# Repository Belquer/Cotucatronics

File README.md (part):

# Cotucatronics OS
<!-- doc-check: ignore no_connect (KiCad ERC violation code) -->
<!-- doc-check: ignore dentro_do_contorno (tool lives in kicad/, out of check_docs' reach) -->
<!-- doc-check: ignore para_fabrica (tool lives in kicad/, out of check_docs' reach) -->
<!-- doc-check: ignore pcb_contorno (tool lives in kicad/, out of check_docs' reach) -->

<!-- doc-check: ignore hook_stop (script in docs/operacao/, not a param) -->
<!-- doc-check: ignore svg_colisoes (tool outside src/. check_docs sweeps `src/`; these live in `tools/`, `docs/desenhos/caixa/` or `kicad/cotuca_cerebro/`, which it does not read. Not a phantom: it is the checker's reach.) -->

Modular firmware for **sound-sculpture instruments**. The core idea is that the
same brain runs any sculpture: the instrument code is board-agnostic, and
changing hardware means writing one new file — not rewriting the system.

A collaborative project.

> ### Status, 2026-09-04 — **v0.301.0**
>
> **480 MHz · 48 kHz · block 48** (1,000 µs deadline) · app in QSPI
>
> **Two character chains** (drive, phaser, warble, tarolator per piezo) over a
> **shared tail** (delay, freeze, shimmer↺reverb), with a **2×2 routing
> matrix** — which chain feeds which output.
>
> **Four-layer anti-feedback stack**, all in shell C++: gate, Governor, limiter
> and SSB shifter — plus **SuMiA™**, the automated microphonic-feedback
> suppressor, four notches per branch, which hunts and fills on its own.
>
> **MIDI across six channels** over a BLE↔UART bridge on an ESP32-C3 (`ch1`
> shared · `ch2` chain A · `ch3` chain B · listen = send + 3), **81 CCs**,
> presets in RAM, **black box** in BACKUP_SRAM.
>
> **Panel soldered and alive:** SSD1309 OLED over SPI with an animated splash,
> **three encoders**, **two pots** (per-branch volume) and **four buttons** with
> two LEDs. The map lives in
> [`docs/operacao/PINOS.md`](docs/operacao/PINOS.md), which is the source — and
> the code is what rules over it.

> ### What has NOT yet passed the ear or the multimeter
>
> - **The compressor has never been heard.** It has existed since 2026-09-02
>   (`dynamics.h`) and has never been switched on with sound.
> - **Four items from the [listening agenda](docs/PAUTA-ESCUTA.md)** — the top
>   of `drv_sujeira` (only ever approved at 0), shimmer with real transposition,
>   the rewritten delay, and ~20 versions with no verdict from the ear.
> - **The broadband hiss** is diagnosed down to a named rule — `AGND`/`DGND`
>   joined off-board, P3 of the ground sweep — and the grounding was redone on
>   2026-09-03 with cleaner sound, **but the multimeter measurement was never made**.
> - **The DPDT commons** are waiting on two continuity checks: is the amp BTL?
>   and is the terminal going to the island a power output or just the TRS
>   sleeve?

---

## Architecture

Five rules that are not negotiable:

1. **HAL boundary.** No vendor `#include` outside `hal_<board>.cpp`.
   `main.cpp`, params, macros and manifests do not know which board they are
   running on. The board is chosen with `make BOARD=daisy_seed`.
2. **Normalized parameters.** Everything is `0.0–1.0` in one central table; the
   manifest is what translates to Hz, seconds, dB.
3. **Macros.** One physical knob can move several parameters, with weight and
   inversion.
4. **Manifest per instrument.** It is the only file that changes from sculpture
   to sculpture. It declares `Requirements` — big RAM, audio in, number of knobs
   — checked at boot: an inadequate board gives a clear error instead of a
   mysterious bug on stage.
5. **`AllocBig()`.** Abstracts the 64 MB of SDRAM. Bump allocator, boot only,
   never in the audio callback. A board without big RAM returns `nullptr` — the
   caller **must** check.

## File map

| File | Version | What it is |
|---|---|---|
| [src/hal.h](src/hal.h) | **v0.45.0** | The contract. The vendor-independence boundary |
| [src/hal_daisy_seed.cpp](src/hal_daisy_seed.cpp) | **v0.86.0** | The only file allowed to include `daisy_seed.h`. **4 buttons** (D26, D24, D25 CTOS rearm, D22 freeze B) and **2 panel LEDs** (D27, D23). 30 ms debounce, measured. **SSD1309 OLED alive** (SPI1: D5 RST · D6 DC · D7 CS · D8 CLK · D10 DIN) with a wire probe and bridge hunter. **Internal PULL-UP on the MIDI RX (PB7)** — libDaisy starts the UART with `GPIO_NOPULL`, and the pin floating with the bridge unplugged put the USART into a framing-error storm and killed the loop in 4 s. **USART1 at priority 1**, below its own DMA stream, or the asynchronous abort never completes. **`DmaListen` rearm with a ceiling and backoff** — without it, it ran at the loop's pace and consumed it (10,029 rearms with a healthy bridge). **Whole framebuffer via `OledDesenha`** (`memcpy`, not 8,192 `DrawPixel` calls), and the SPI prescaler is born at **PS_8** — 3,811 µs per frame, verified on the glass with a 1 px pattern. PS_64 cost 23,401 µs. **ONE encoder** since 2026-09-05 (there were three; dB closed the interface down to one, and that dissolved the `D17` conflict for free — it was both the G encoder's push *and* the A2 of the rail divider) — and `kEncPin` is the SINGLE source: `Init` reads from it and the names come out of `EncoderPinNome`. **`VarreTudo`** reads all 31 pins (kills OLED and MIDI until a reboot) and **`Reiniciar`** undoes it. `PollMidi`/`PollSerial` drain from a **snapshot** of the pointer — chasing the live pointer locked the board up on 2026-08-28 |
| [src/reverb.h](src/reverb.h) | **v0.2.0** | Freeverb + high-pass. Pure C++, buffers come from outside |
| [src/freeze.h](src/freeze.h) | **v0.3.1** | Granular freeze: 500 ms core, 2 randomly placed grains, Hann. Pure C++ |
| [src/pitch.h](src/pitch.h) | **v0.5.0** | Shared pitch engine: 1 buffer, up to 4 voices. **Automatic anti-aliasing on write** (6th-order Butterworth, zero cost if no voice shifts up). Pure C++ |
| [src/shimmer.h](src/shimmer.h) | **v0.3.0** | Shimmer: reverb + pitch in a loop. Feeds back into the existing Freeverb. **Tone = cut + presence bell at 3 kHz** |
| [src/drive.h](src/drive.h) | **v0.4.1** | Drive: normalized tanh, **1.5–48×** (the knee has to reach −30 dBFS), plus `drv_sujeira`: a morph into a wavefolder with its own anti-aliasing |
| [src/phaser.h](src/phaser.h) | **v0.3.0** | Phaser: N allpasses swept by a triangular LFO. Zero buffer |
| [src/warble.h](src/warble.h) | **v0.1.1** | Warble: tape drift via a short modulated delay. Its dry/wet is called `wrb_mix` and **that is a name, not a param** |
| [src/detune.h](src/detune.h) | **v0.1.0** | Detune. **OUT of the build since 2026-08-20** — revivable, see `docs/FEATURES.md` |
| [src/delay.h](src/delay.h) | **v0.2.0** | Delay in C++: 1 s line, fixed 0.4 feedback, 50 ms floor. **Read clamped against NaN/Inf, with a `clamps_` counter** |
| [src/effect_slot.h](src/effect_slot.h) | **v0.3.0** | The frame: asymmetric fade, zero cost when off, timing |
| [src/pitch_spectrum.py](src/pitch_spectrum.py) | **v0.2.0** | The N largest spectral peaks — the dominant peak lies when the sidebands are strong |
| [src/dynamics.h](src/dynamics.h) | **v0.6.0** | Gate, governor, limiter and **SSB shifter**. Pure C++ |
| [src/midi.h](src/midi.h) | **v0.9.0** | MIDI state machine + **the six channels** and the `listen = send + 3` invariant, locked down with a `static_assert`. Pure C++, board-agnostic |
| [src/test_dynamics.cpp](src/test_dynamics.cpp) | **v0.1.0** | Native test bench — runs on the Mac, no board |
| [src/test_midi.cpp](src/test_midi.cpp) | **v0.6.0** | Native bench for the MIDI parser and the CC→ParamTable path |
| [run/test.command](run/test.command) | **v0.4.0** | Double-clickable wrapper for both test benches |
| [src/main.cpp](src/main.cpp) | **v0.329.0** | Loop, audio callback, fake panel over serial. Two chains + shared tail. **MIDI mirror across six channels** (`listen = send + 3`) with a 250 ms authorship window, a `vistos` inventory, physical freeze buttons, `qspi` probes, and a **2×2 routing matrix** (which chain feeds which output, with the ramps in a buffer so the dry, the freeze and the space all read the same value). **The version lives only in `COTUCA_OS_VERSION`** |
| [src/suave.h](src/suave.h) | **v0.1.0** | One-pole parameter smoother. Pure C++ — the fourth occurrence of the shape turning into a single one |
| [src/teste_tarol.cpp](src/teste_tarol.cpp) | **v0.2.0** | Native bench for the tarolator. **Declares what it does NOT prove**: it passed with sine waves while the effect sounded like a snare drum — a bench proves the algebra, not the timbre (scar 15u) |
| [src/teste_macro.cpp](src/teste_macro.cpp) | **v0.1.1** | Round trip of `Macro::Inverso`, which pot capture depends on. If it is wrong, the pot "doesn't catch" and the bench blames the ADC |
| [src/notch.h](src/notch.h) | **v0.2.0** | **Anti-microphonic notch**, two notches per chain, fixed Q 35, depth in dB. A peaking EQ with negative gain (and not a true notch, which has no adjustable depth). It was born out of a **solid-bodied** piece — exciter and piezo on the same plate, with no joint to lose energy in, which is why no mechanical gesture worked. It goes **before the gate**: if the feedback got through the gate, it would be the thing holding it open |
| [src/splash.h](src/splash.h) | **v0.11.1** | **The splash**: a cowrie-shell cast that falls from above in a fan, **settles**, and then one of the shells rises and grows until it becomes the mark — name letter by letter, version signing itself, mark held for 3 s. Seeded from the **ADC's own noise**, so every boot is a different cast. Three states: full splash at boot, **immediate** preset panel in normal use, and **the cast alone** when the cowries are really thrown. 20 Hz, **pure** C++, step marked `noinline`. **The mark is three pieces, not one**: a hollow shell (a ring made as *filled minus filled* — a double outline does not close at the tops), the lip mass with a `sin(π·t^1.5)` envelope, and the mouth opened only inside the lip, with **paired** upper/lower teeth biting half a gap. Top↔bottom mirror **0 px out of 1,215, measured**; the left↔right asymmetry is deliberate and was chosen by dB from a scale of measured tails. Mark bounding box: **45 × 27 px** at `cy=17` |
| [src/desenho.h](src/desenho.h) | **v0.3.1** | Primitives over the 1,024-byte framebuffer: `Pixel/Le/Linha/Retangulo/Caixa/Elipse/SuperElipse/Texto/Largura/TextoCentrado`. **Integer** Bresenham, no floats — the drawing on the board is bit-for-bit the one in the ground test. **Clipping lives only in `Pixel`**, not an `if` per primitive, which is how one gets forgotten. In `SuperElipse`, **a row of pixels is a band and not an edge** (width measured at `|y|−0.5`) and **the cap is a stroke** — it was the apex spike that, once removed, opened the outline at the top |
| [src/fonte5x7.py](src/fonte5x7.py) → [src/fonte5x7.h](src/fonte5x7.h) | **v0.1.0** | 43 glyphs as **readable art**, not blind hex; `--ver` redraws from the generated result, which closes the loop. A character with no glyph draws a **box**, never a space: a silently missing glyph is indistinguishable from correct text |
| [src/espectro.h](src/espectro.h) | **v0.2.0** | Hand-written radix-2 FFT, Hann, peak with **parabolic interpolation in dB**, and **dominance** — the fraction of energy at the peak, which separates a spike from a note. It replaced an autocorrelation that failed **6 out of 6** in the trial (peaks at multiples, and it measures periodicity instead of partial strength) |
| [src/tarol.h](src/tarol.h) | **v0.1.0** | **TAROLATOR** — percussive noise with the envelope of the strike, by frequency division. It was born as an octaver and does not do octaves: on a membrane the modes are inharmonic and the divider wobbles. The name is dB's, and the name is the diagnosis. Tone and tracking are FIXED: as params they gave dead travel |
| [src/params.h](src/params.h) | **v0.12.0** | `ParamTable` + `Macro` (ceiling **128** since 2026-08-28, raised with 91 occupied — headroom by hand, not after the overflow). No dynamic allocation |
| [src/manifest.h](src/manifest.h) | **v3.0.0** | Two chains, shared character params, per-channel switch and dry/wet, **95 bindings across 55 CCs**, spread over six channels + CC 120 = sync. **Physical button table** (`BotaoAlvo`: param + LED + name) |
| [docs/operacao/gerar_ccmap.py](docs/operacao/gerar_ccmap.py) | **v0.11.0** | **Owner of `CCMAP.md` AND of the A4 `ccmap.html` card** — it writes both from `manifest.h`, and **stamps the date, the commit and a dirty-tree warning** (dB's rule, 2026-09-04). The only hand-written part is the `NOTAS` table, and the generator flags an orphan note and a note that lies about topology ("shared" on a paired param). It found ten wrong notes on its first run. ⚠️ Do not write another one: on 2026-09-04 I wrote a second without looking for this one, and `CCMAP.md` itself said on its 3rd line which was the right one |
| [docs/ccmap.pdf](docs/ccmap.pdf) | **generated** | **The reference card** — 91 bindings across 52 CCs on one A4 sheet, with pairs collapsed. `ccmap.html` is **generated** by `gerar_ccmap.py`; the PDF comes out of `ccmap-pdf.sh` / `.command` v0.1.0, which warns if it runs past one sheet |
| [docs/operacao/RETRABALHO-LOOPY.md](docs/operacao/RETRABALHO-LOOPY.md) | **generated** | The full map for remapping Loopy: 86 bindings across 49 CCs, by page |
| [esp32/ponte/ponte.ino](esp32/ponte/ponte.ino) | **v1.7.0** | **The second firmware.** BLE MIDI ↔ UART bridge on the ESP32-C3 — a wire with a radio: no CC map, no params. D28 active low, open-drain. `board` reports dropouts with recency and TX saturations, and since v0.5.0 **dropouts that survive a power cut** (NVS, deferred write): one count for this session, another for all time with the number of boots |
| [esp32/README.md](esp32/README.md) | — | Wiring, chosen pins, how to flash, and the environment known to work (⚠️ NimBLE **1.4.3**; 2.x does not compile) |
| [docs/operacao/ATERRAMENTO.md](docs/operacao/ATERRAMENTO.md) | **v0.2.0** | **The grounding chapter** — the three conductor types and the legal destination of each, star versus daisy chain, `AGND`/`DGND` and the narrow bridge, capacitors **by load type** (what the amp demands, the step-down refuses and the radio needs), high-impedance inputs, coupling through the air, and the measurement method **under load**. It owns the subject: when it disagrees with `HARDWARE.md`, it wins |
| [docs/operacao/GEAR-AUDIT.md](docs/operacao/GEAR-AUDIT.md) | **v0.1.0** | The decision to swap the WIDI Core for an ESP32-C3: US$ 45 → US$ 4 on a part replicated in series. **No plan B — acceptance is the gate**, and what it blocks is the order |
| [docs/operacao/VOO-ESP32-PONTE.md](docs/operacao/VOO-ESP32-PONTE.md) | **v0.1.0** | The BLE↔UART bridge flight. **The Daisy firmware does not change one line** — automatic `sync` is flight 2. Carries the three checks made before writing any code |
| [docs/operacao/gerar_projeto_loopy.py](docs/operacao/gerar_projeto_loopy.py) | **v0.2.0** | **Writes a COMPLETE `.lpproj`** from `manifest.h` — 9 pages, 143 widgets, colours by channel. It starts from a template and preserves the loop scene and the whole bundle: a project without `Clock` or `Sequence` will not even open. **Never writes over the template** |
| [docs/operacao/gerar_perfil_loopy.py](docs/operacao/gerar_perfil_loopy.py) | **v1.0.1** | Reads the project exported from Loopy (`.lpproj`, a zip with SQLite) and **emits the bindings** already addressed, with the CCs coming from `manifest.h`. ⚠️ The address is positional — regenerate after touching the layout |
| [docs/operacao/gerar_secao_loopy.py](docs/operacao/gerar_secao_loopy.py) | **v0.3.0** | **Owner of `LOOPY-SECAO.md`** — the build sheet for the new section, with CC, channel, widget type, range and birth value, plus the presets page. Generated because **six CCs** changed in a single session: a hand-written sheet drifts at the first change, and whoever follows it builds yesterday's instrument |
| [docs/operacao/LOOPY-SECAO.md](docs/operacao/LOOPY-SECAO.md) | **generated** | The bindings in learning order — it is not a layout: Loopy addresses by array index, which only exists once the widgets have been created. ⚠️ The count is **declared by the file itself** (today: 114) and is deliberately not repeated here — this row used to say 105, and restating a generated file's counts is exactly how the two drift apart |
| [docs/operacao/CCS-POR-PAGINA.md](docs/operacao/CCS-POR-PAGINA.md) | **generated** | The CCs in the order of Loopy's pages: central / mod a / mod b / time a / time b / random / tech |
| [docs/operacao/BINDINGS-A-MAO.md](docs/operacao/BINDINGS-A-MAO.md) | **generated** | Plan B: a manual entry sheet for Control Settings, with CC and channel per row |
| [docs/operacao/ACEITE-MULTIPLEXACAO.md](docs/operacao/ACEITE-MULTIPLEXACAO.md) | **living** | The MIDI acceptance script — the firmware side is green |
| [src/presets.h](src/presets.h) | **v0.11.0** | Preset structures and the **derived map version** (FNV-1a of the names; today **`0xBE1B`**). Pure C++ — provable end to end on a native bench. Preset membership is DERIVED from the name, and `route_*` is on the short exception list. Per-preset ceiling **56** |
| [src/test_presets.cpp](src/test_presets.cpp) | **v0.7.0** | Native preset bench: membership, hash (both halves) and every refusal verdict |
| [src/qspi_raw.h](src/qspi_raw.h) | **v0.10.0** | Contract for raw QUADSPI access. **Zero transitive closure** — nothing it calls may live in QSPI |
| [src/qspi_raw.cpp](src/qspi_raw.cpp) | **v0.10.0** | QUADSPI registers by hand, everything marked `COTUCA_ITCM`. **Erases, programs and reads** (`qspi prova` passes on the board). Leaving memory-mapped mode is **`CR.EN=0`, NOT `ABORT`** — and you also have to **leave continuous read** (`ABR=0x00`) or the chip does not hear opcodes. Safe zone enforced in code. See `docs/DESENHO-ESCRITA-QSPI.md` and scar 15fw |
| [src/cotucatronics_qspi.lds](src/cotucatronics_qspi.lds) | **v0.1.0** | Linker script forked from libDaisy (provenance note at the top). Adds `.itcm_text` → ITCMRAM |
| [src/teste_minimo/](src/teste_minimo/) | **v0.4.0** | **On-board proving bench.** Thirty lines that cut the problem in half in one flash: if it talks, the chain is good and the defect belongs to the app. It has already ruled out the board, the flashing, USB, audio init and 64 MB of SDRAM — and it prints what `CheckBoardVersion()` detected |
| [run/grava_placa_nova.command](run/grava_placa_nova.command) | **v0.2.0** | Flashes a **new** Daisy, whether factory-fresh or already carrying a bootloader — `flash.sh` only works once there is an app running. It waits for DFU and **decides the target from the memory map**, not from the PID: `0x90000000` is QSPI (bootloader present → `program-dfu`), `0x08000000` is ST's ROM (→ `program-boot`). ⚠️ Both DFUs enumerate as `0483:df11` — `STM_PID` and `DAISY_PID` are the **same value**, and discriminating by PID means flashing the bootloader over a board that only wanted the app. **The `program-boot` branch has never been exercised** |
| [src/flash.sh](src/flash.sh) | **v0.4.0** | Flashes **only if the build passed**, checks the version **in the source and on the board**, and **restores the state the flash wiped**. It enters the bootloader via `dfu go` and waits for DFU to appear, instead of asking for a RESET |
| [src/estado.py](src/estado.py) | **v0.2.0** | Saves the params before DFU and restores them after. ⚠️ It speaks in **`real`**, which is what `set` accepts — v0.1.0 sent `norm`, was refused with `out of range`, and **printed "restored" anyway** because I was throwing the reply away. It reads the reply, and shouts about whatever is refused |
| [src/porta_daisy.py](src/porta_daisy.py) | **v0.1.0** | Finds the Daisy **by asking**, never by position in the `glob`. It was born when the ESP32 joined the USB bus and there were suddenly two `usbmodem` devices — choosing by index became luck |
| [docs/operacao/auditar.sh](docs/operacao/auditar.sh) · [.command](run/auditar.command) | **v1.3.0** | **The mechanical sweep of `/audit`** — dead links, orphan exemptions, orphan and duplicate retirements, desynchronized destinations (repo/vault), `check_docs` and the version map. **It only reports what it can prove**: the judgement classes live in the skill, not here. On its first run it found 5 dead links in `MAPA-DE-TERRA.md` and one duplicate entry |
| [docs/operacao/hook_stop.sh](docs/operacao/hook_stop.sh) · [.claude/settings.json](.claude/settings.json) | **v1.0.0** | **`/audit` runs on its own at the end of every session, and WARNS.** `battle_scars` already had the rule — *"an automated habit beats a remembered habit"* — and every checker depended on somebody remembering. **It never blocks:** it always exits 0, because a gate that gets in the way is a gate that gets switched off. ⚠️ The count is **per section** — the pending-items pass lists 🔴/🟡 that live inside the documents, and counting them would mean a permanent alarm |
| [docs/operacao/hook_commit.sh](docs/operacao/hook_commit.sh) | **v1.0.0** | **The CHEAP checkers run before the commit** — `PreToolUse` on `git commit`, **70 ms**. `hook_stop` already caught these things, but at the end of the session, with the bad one already pushed: **the gain is not avoiding the mistake, it is having it arrive while there is still context to fix it.** It runs only the version map (0.03 s) and drawing freshness (0.02 s); `check_docs` (1.5 s) and `auditar` (3.3 s) stay at the close — an expensive check on every commit is a check that eventually gets removed. It warns, never blocks. On its first run it caught a stale drawing nobody knew was stale |
| [docs/operacao/derivados.py](docs/operacao/derivados.py) | **v1.2.0** | **Makes "generated" a refutable claim.** `manifest.h` was already the single source and the CC map gave different numbers in different documents — the cause was the label: three sheets claimed to be generated from it, nobody maintained them by hand *because of that*, and **no generator wrote them**. It checks who claims to be derived, from which version of the source, whether it matches today's, and **whether a generator exists that writes it**. The stamp that works names the SOURCE (`manifest v1.13.0`), not the generator |
| [docs/operacao/vizinhos.py](docs/operacao/vizinhos.py) | **v1.0.0** | Hunts the **sentence broken by a rename** — the case where the anchor matched, `grep` confirmed, `make` passed, and the sentence lost its meaning because the continuation was on the next line. It only flags when the edit touched the **end** of the line; `--termo=<name>` narrows it to where the removed tail carried the name (211 → 89 → 16 neighbourhoods) |
| [docs/operacao/coerencia.py](docs/operacao/coerencia.py) | **v1.1.0** | The checks `grep` does not do properly — exemptions that cover nothing (by `check_docs`' criterion: **between backticks**, file scope), health of the retirement list, and the **pending-items pass**. It was born fixing two bash checks that were accusing by the wrong criterion |
| [docs/operacao/versoes_readme.py](docs/operacao/versoes_readme.py) | **v1.2.0** | Checks the file map above against the files — `CLAUDE.md` demands the current version on every row and nothing was enforcing it. `--write` fixes them. **On its first run: 15 of 58 had drifted**, one of them with the README AHEAD of the source (`ponte.ino`). It reports what it cannot read, instead of skipping silently |
| [src/check_docs.py](src/check_docs.py) | **v0.14.0** | `make check-docs`: puts the docs on the stand against the manifest — phantoms, commands without help text, the pin map, ranges, and **two versions in the same file that disagree**. It aborts if `AddMidi` matches nothing. **It prints its own version on the first line**. The two-versions rule also covers `.py`, where there is no `#define`: it cross-checks the docstring, the constant and **what the script prints** |
| [docs/params-aposentados.txt](docs/params-aposentados.txt) | **living** | Retired params, removed symbols and external names — what the checker has licence not to find |
| [docs/DESENHO-ESCRITA-QSPI.md](docs/DESENHO-ESCRITA-QSPI.md) | **living** | The preset route: **RESOLVED on 2026-09-29** — the window, the complete command table, the sequence that works, and why libDaisy refuses to write to QSPI when the program is running from it |
| [docs/FUTURO.md](docs/FUTURO.md) | **living** | **Possibilities, with the cost already established** — it is not a task list: it is what was considered and why it is not now. DPDT sense, a colour screen, the encoders that were removed, and the **budget of ten free pins** everything comes out of. It exists because the alternative is rediscovery: three times in one week a question was reopened that already had a measured answer, kept only in a conversation |
| [docs/PAUTA-ESCUTA.md](docs/PAUTA-ESCUTA.md) | **living** | What to listen to, in order — ~20 versions with no verdict from the ear |
| [src/Makefile](src/Makefile) | **v0.2.0** | Per-board build. `APP_TYPE=BOOT_QSPI`. No DaisySP |
| [.claude/skills/](.claude/skills/) | **living** | **The executable arm of IFÁ10000** — **fifteen** skills: **`aipcb`**, `ifa10000`, `medicao-limpa`, `instrumentacao`, `bug-de-ordem`, `edicao-segura`, `bancada-firmware`, `revisao-terra`, `kicad_layout`, `loopy`, `design-review`, `audit`, `caixa`, `pm`, plus the headstone of `kicad`. ⚠️ **`kicad` was RETIRED on 2026-09-09** and replaced by `aipcb` — its 1,033 lines are in [docs/rev_b/kicad-skill-aposentada.md](docs/rev_b/kicad-skill-aposentada.md), and only the headstone remains in `.claude/skills/kicad/`. The underlying difference: `kicad` described generators that wrote KiCad files by hand; `aipcb` describes a flow in which **nobody** writes KiCad files by hand. ⚠️ **`kicad_layout` was left with nobody to call it** — it said "called by the `kicad` skill", and `aipcb` does not mention it. Decision pending: it joins `aipcb`, it gets retired too, or it stays |
| [docs/desenhos/](docs/desenhos/) · [tools/desenhos.py](tools/desenhos.py) | **v0.4.0** | **The technical-drawing folder, and the tool that keeps it honest.** The schematics come out of `kicad-cli sch export svg` — the same source the factory reads, so they **cannot diverge**. `desenhos.py` compares dates: **if the source is newer than the drawing, the drawing is stale**, and it exits non-zero. No opinion in the criterion. ⚠️ These do not pass `svg_colisoes` (KiCad writes letters as *paths*) — we traded *"it can diverge but it gets checked"* for *"it cannot diverge but it does not get checked"*, and that is declared. `preamp-piezo.svg` died on 2026-09-05 for saying `C2 1 nF` and `RV1` alive when the schematic already said `20n` and `DNP` — **an out-of-date figure with an official look is worse than none** |
| [docs/operacao/PINOS.md](docs/operacao/PINOS.md) | **living** | **The pin map, and the source is the code.** Checked at every `bts`. On 2026-09-04 it was caught saying `Free: D0–D12` while listing the OLED as occupied three sections below — genuinely free is six |
| [docs/operacao/SUPRESSOR-MICROFONIA.md](docs/operacao/SUPRESSOR-MICROFONIA.md) | **living** | The **SuMiA™** contract, measured before the code, plus what it has already done in service |
| [docs/operacao/TERRA-REFAZER.md](docs/operacao/TERRA-REFAZER.md) | **living** | The ground sweep and the bench sheet the grounding was redone with on 2026-09-03. Pairs with [ATERRAMENTO.md](docs/operacao/ATERRAMENTO.md) above, which owns the subject |
| [docs/operacao/ARQUITETURA.md](docs/operacao/ARQUITETURA.md) | **living** | The signal design, end to end |
| [docs/operacao/PRESETS.md](docs/operacao/PRESETS.md) · [DESENHO-PRESETS-RAM.md](docs/operacao/DESENHO-PRESETS-RAM.md) · [PRESETS-LISTA.md](docs/operacao/PRESETS-LISTA.md) | **living** | Presets: the contract, the RAM design, and the list |
| [docs/operacao/REMAP-ESCUTA.md](docs/operacao/REMAP-ESCUTA.md) · [ROTINAS.md](docs/operacao/ROTINAS.md) | **living** | The listening remap and the bench routines |
| [docs/operacao/esquematicos/](docs/operacao/esquematicos/) | **living** | The carrier board in KiCad — `brief` and `bom` for revA, `brief` and `ERC-ISENCOES` for revB. Drawing rules in the `kicad` skill |
| [caixa/cotuca_caixa_corte.py](caixa/cotuca_caixa_corte.py) | **v0.7.0** | **The source of the enclosure.** It generates the cut from `--t` and `--kerf` — changing material means regenerating, because the tooth depth IS the thickness. The filename carries the thickness. Three gates of its own: nesting, **mirror** (a part that was rotated but in fact mirrored cuts fine and assembles backwards) and margin to the sheet edge. Three-shelf nesting computed from the real bounding boxes — at T=3 the parts grow and the old column left 1.4 mm of margin |
| [caixa/](caixa/) · [tools/nesting.py](tools/nesting.py) | **v0.1.0** | The rest of the physical artefact, and the external gate: everything inside the sheet, nothing overlapping, and **the part count** — an absence does not collide. ⚠️ On 2026-09-06 the 6 fabrication pages, their generators and the walnut cut all died: they drew, or they were, **another** enclosure, and a superseded source alongside the right one measures just as well |
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
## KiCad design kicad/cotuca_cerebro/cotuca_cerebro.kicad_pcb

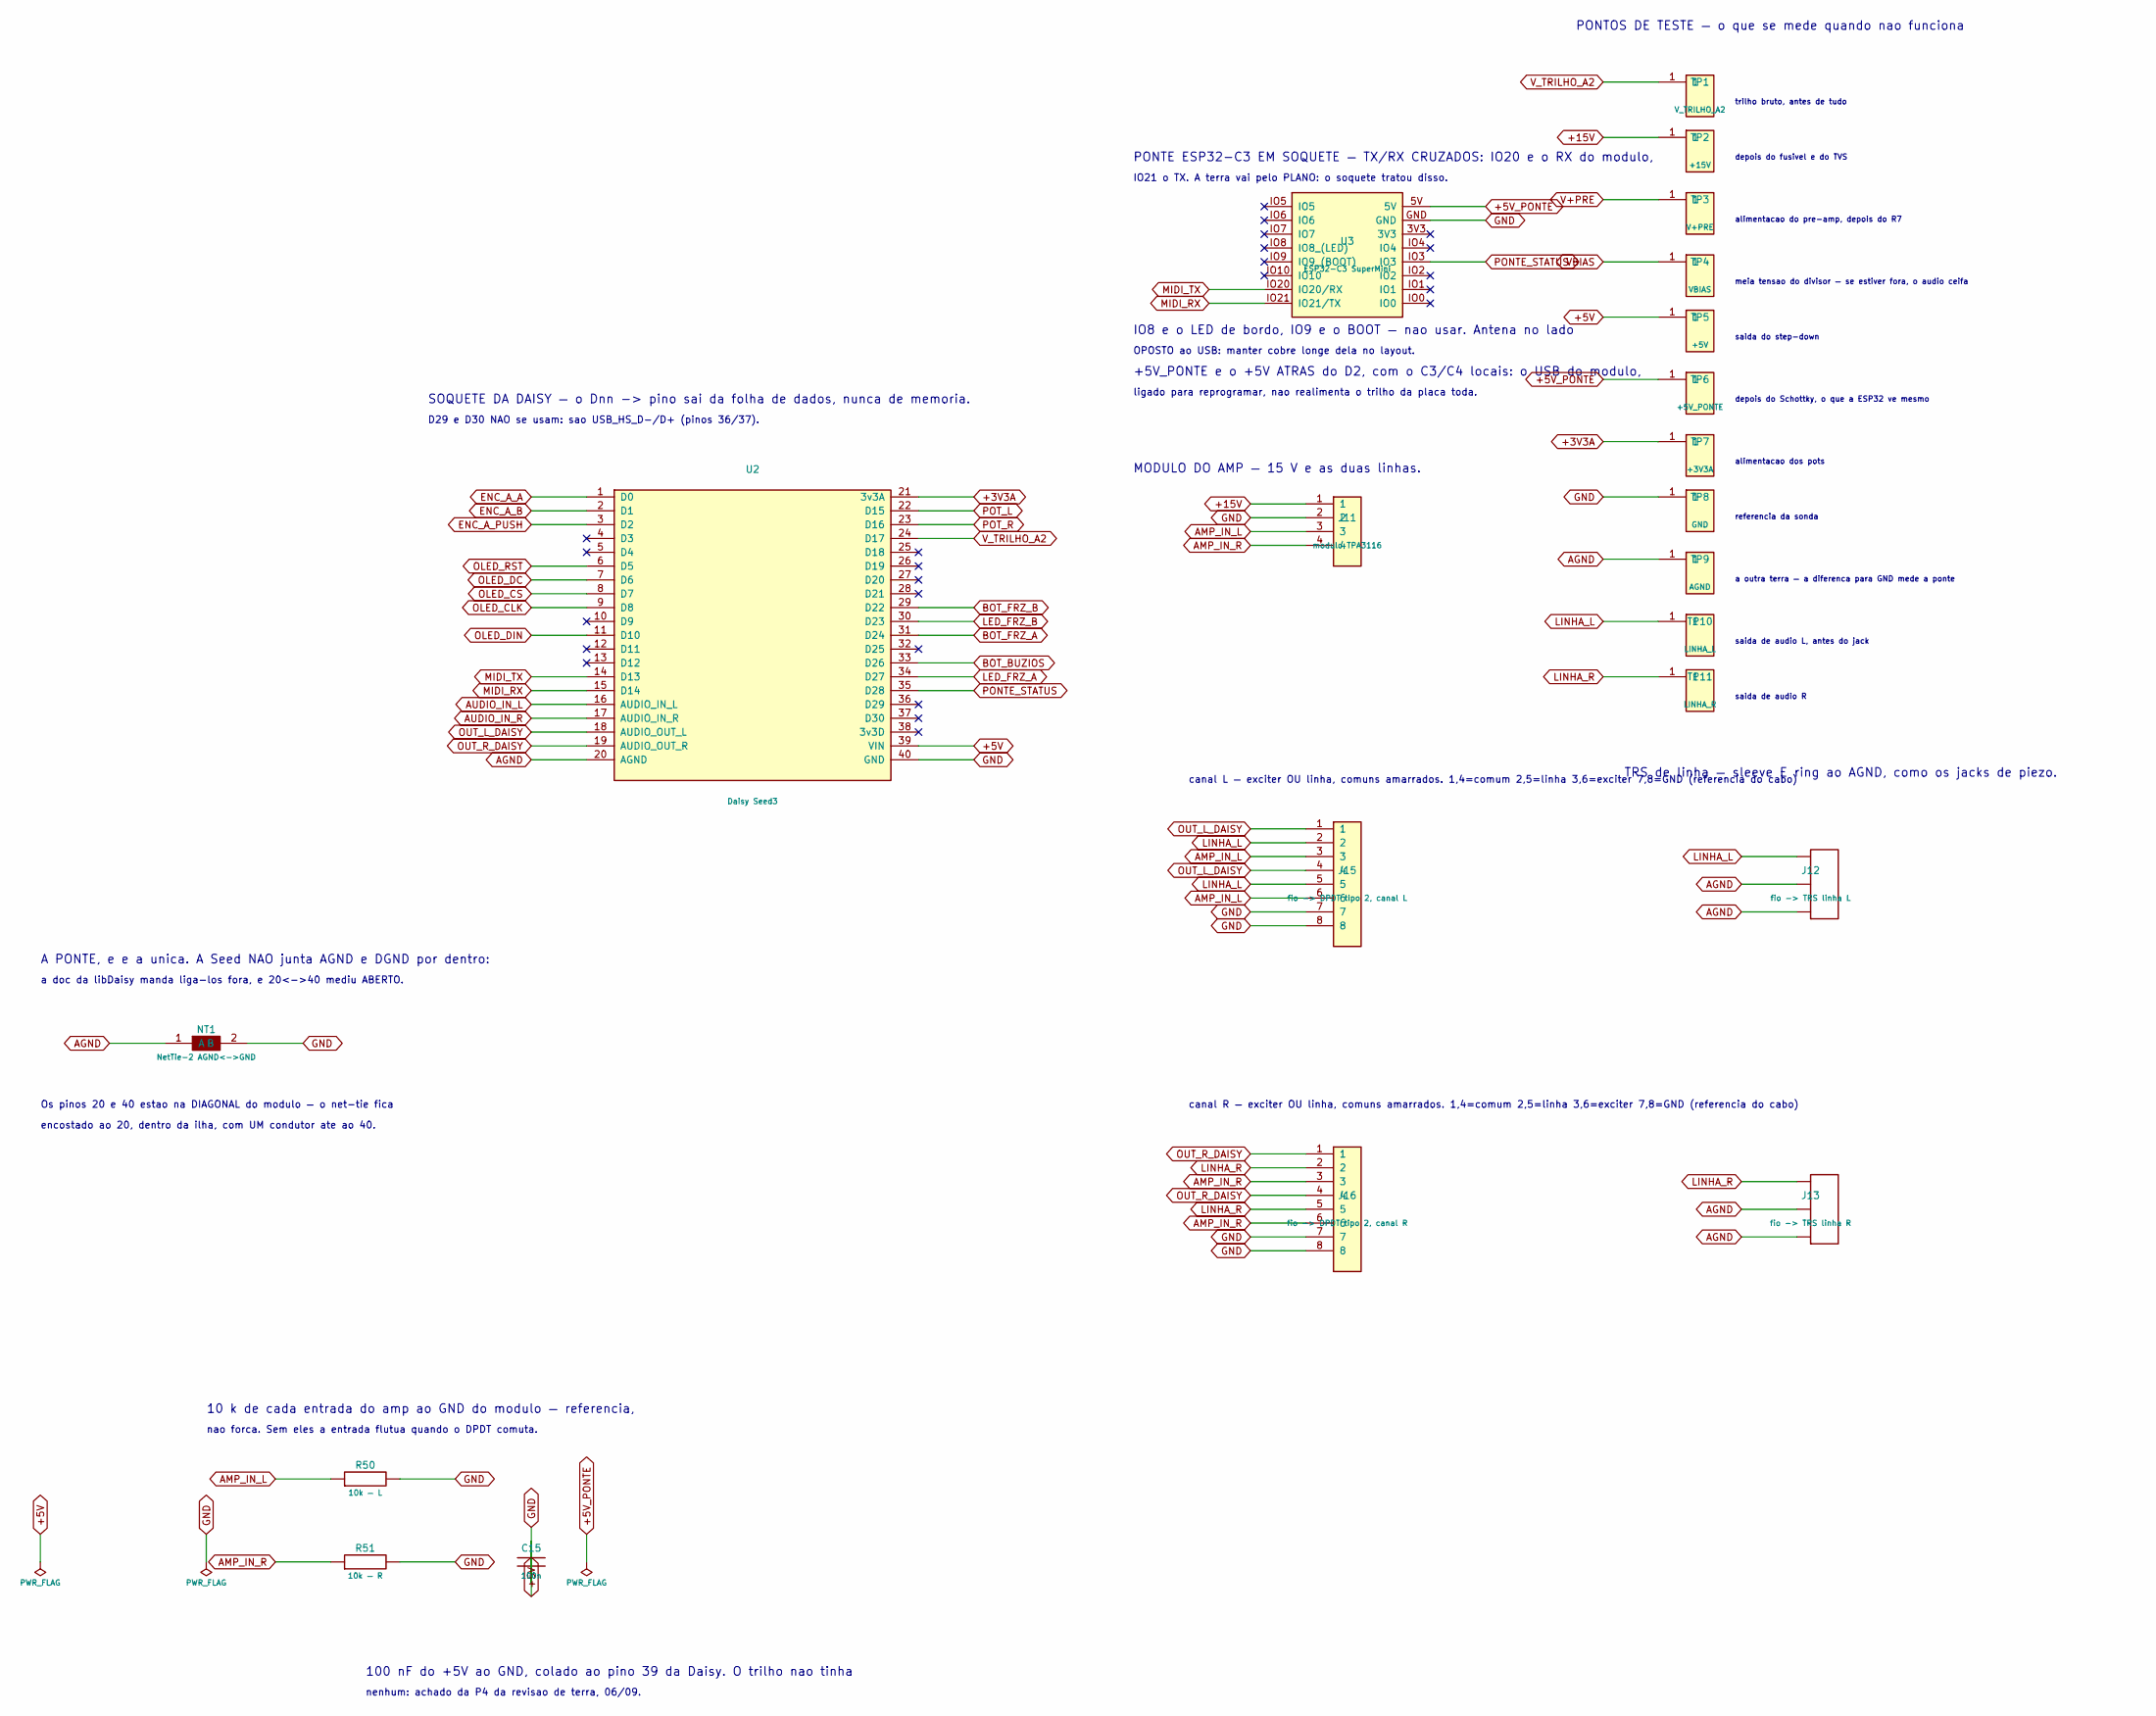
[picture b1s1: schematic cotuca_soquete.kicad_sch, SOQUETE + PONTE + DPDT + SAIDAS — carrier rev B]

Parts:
C15: 100n; C_0805_2012Metric
J11: modulo TPA3116; PinHeader_1x04_P2.54mm_Vertical; MPN 61304011121
J12: fio -> TRS linha L; PinHeader_1x03_P2.54mm_Vertical; MPN 61304011121
J13: fio -> TRS linha R; PinHeader_1x03_P2.54mm_Vertical; MPN 61304011121
J15: fio -> DPDT tipo 2, canal L; PinHeader_1x08_P2.54mm_Vertical; MPN 61304011121
J16: fio -> DPDT tipo 2, canal R; PinHeader_1x08_P2.54mm_Vertical; MPN 61304011121
NT1: NetTie-2 AGND<->GND; NetTie-2_SMD_Pad2.0mm
R50: 10k — L; R_0805_2012Metric
R51: 10k — R; R_0805_2012Metric
TP1: V_TRILHO_A2; TestPoint_Pad_D1.5mm
TP2: +15V; TestPoint_Pad_D1.5mm
TP3: V+PRE; TestPoint_Pad_D1.5mm
TP4: VBIAS; TestPoint_Pad_D1.5mm
TP5: +5V; TestPoint_Pad_D1.5mm
TP6: +5V_PONTE; TestPoint_Pad_D1.5mm
TP7: +3V3A; TestPoint_Pad_D1.5mm
TP8: GND; TestPoint_Pad_D1.5mm
TP9: AGND; TestPoint_Pad_D1.5mm
TP10: LINHA_L; TestPoint_Pad_D1.5mm
TP11: LINHA_R; TestPoint_Pad_D1.5mm
U2: Daisy Seed3; Electrosmith_Daisy_Seed
U3: ESP32-C3 SuperMini; ESP32C3_SUPERMINI_SOQUETE

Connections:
+3V3A: TP7.1, U2.21 (3v3A); also elsewhere on the board
+5V: C15.1, TP5.1, U2.39 (VIN); also elsewhere on the board
+5V_PONTE: TP6.1, U3.5V; also elsewhere on the board
+15V: J11.1, TP2.1; also elsewhere on the board
AGND: J12.2, J12.3, J13.2, J13.3, NT1.1 (A), TP9.1, U2.20 (AGND); also elsewhere on the board
AMP_IN_L: J11.3, J15.3, J15.6, R50.1
AMP_IN_R: J11.4, J16.3, J16.6, R51.1
AUDIO_IN_L: U2.16 (AUDIO_IN_L); also elsewhere on the board
AUDIO_IN_R: U2.17 (AUDIO_IN_R); also elsewhere on the board
BOT_BUZIOS: U2.33 (D26); also elsewhere on the board
BOT_FRZ_A: U2.31 (D24); also elsewhere on the board
BOT_FRZ_B: U2.29 (D22); also elsewhere on the board
ENC_A_A: U2.1 (D0); also elsewhere on the board
ENC_A_B: U2.2 (D1); also elsewhere on the board
ENC_A_PUSH: U2.3 (D2); also elsewhere on the board
GND: C15.2, J11.2, J15.7, J15.8, J16.7, J16.8, NT1.2 (B), R50.2, R51.2, TP8.1, U2.40 (GND), U3.GND; also elsewhere on the board
LED_FRZ_A: U2.34 (D27); also elsewhere on the board
LED_FRZ_B: U2.30 (D23); also elsewhere on the board
LINHA_L: J12.1, J15.2, J15.5, TP10.1
LINHA_R: J13.1, J16.2, J16.5, TP11.1
MIDI_RX: U2.15 (D14), U3.IO21 (IO21/TX)
MIDI_TX: U2.14 (D13), U3.IO20 (IO20/RX)
OLED_CLK: U2.9 (D8); also elsewhere on the board
OLED_CS: U2.8 (D7); also elsewhere on the board
OLED_DC: U2.7 (D6); also elsewhere on the board
OLED_DIN: U2.11 (D10); also elsewhere on the board
OLED_RST: U2.6 (D5); also elsewhere on the board
OUT_L_DAISY: J15.1, J15.4, U2.18 (AUDIO_OUT_L)
OUT_R_DAISY: J16.1, J16.4, U2.19 (AUDIO_OUT_R)
PONTE_STATUS: U2.35 (D28), U3.IO3
POT_L: U2.22 (D15); also elsewhere on the board
POT_R: U2.23 (D16); also elsewhere on the board
V+PRE: TP3.1; also elsewhere on the board
VBIAS: TP4.1; also elsewhere on the board
V_TRILHO_A2: TP1.1, U2.24 (D17); also elsewhere on the board

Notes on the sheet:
SOQUETE DA DAISY — o Dnn -> pino sai da folha de dados, nunca de memoria.
D29 e D30 NAO se usam: sao USB_HS_D-/D+ (pinos 36/37).
A PONTE, e e a unica. A Seed NAO junta AGND e DGND por dentro:
a doc da libDaisy manda liga-los fora, e 20<->40 mediu ABERTO.
Os pinos 20 e 40 estao na DIAGONAL do modulo — o net-tie fica
encostado ao 20, dentro da ilha, com UM condutor ate ao 40.
PONTE ESP32-C3 EM SOQUETE — TX/RX CRUZADOS: IO20 e o RX do modulo,
IO21 o TX. A terra vai pelo PLANO: o soquete tratou disso.
IO8 e o LED de bordo, IO9 e o BOOT — nao usar. Antena no lado
OPOSTO ao USB: manter cobre longe dela no layout.
+5V_PONTE e o +5V ATRAS do D2, com o C3/C4 locais: o USB do modulo,
ligado para reprogramar, nao realimenta o trilho da placa toda.
MODULO DO AMP — 15 V e as duas linhas.
canal L — exciter OU linha, comuns amarrados. 1,4=comum 2,5=linha 3,6=exciter 7,8=GND (referencia do cabo)
canal R — exciter OU linha, comuns amarrados. 1,4=comum 2,5=linha 3,6=exciter 7,8=GND (referencia do cabo)
trilho bruto, antes de tudo
depois do fusivel e do TVS
alimentacao do pre-amp, depois do R7
meia tensao do divisor — se estiver fora, o audio ceifa
saida do step-down
depois do Schottky, o que a ESP32 ve mesmo
alimentacao dos pots
referencia da sonda
a outra terra — a diferenca para GND mede a ponte
saida de audio L, antes do jack
saida de audio R
PONTOS DE TESTE — o que se mede quando nao funciona
10 k de cada entrada do amp ao GND do modulo — referencia,
nao forca. Sem eles a entrada flutua quando o DPDT comuta.
TRS de linha — sleeve E ring ao AGND, como os jacks de piezo.
100 nF do +5V ao GND, colado ao pino 39 da Daisy. O trilho nao tinha
nenhum: achado da P4 da revisao de terra, 06/09.

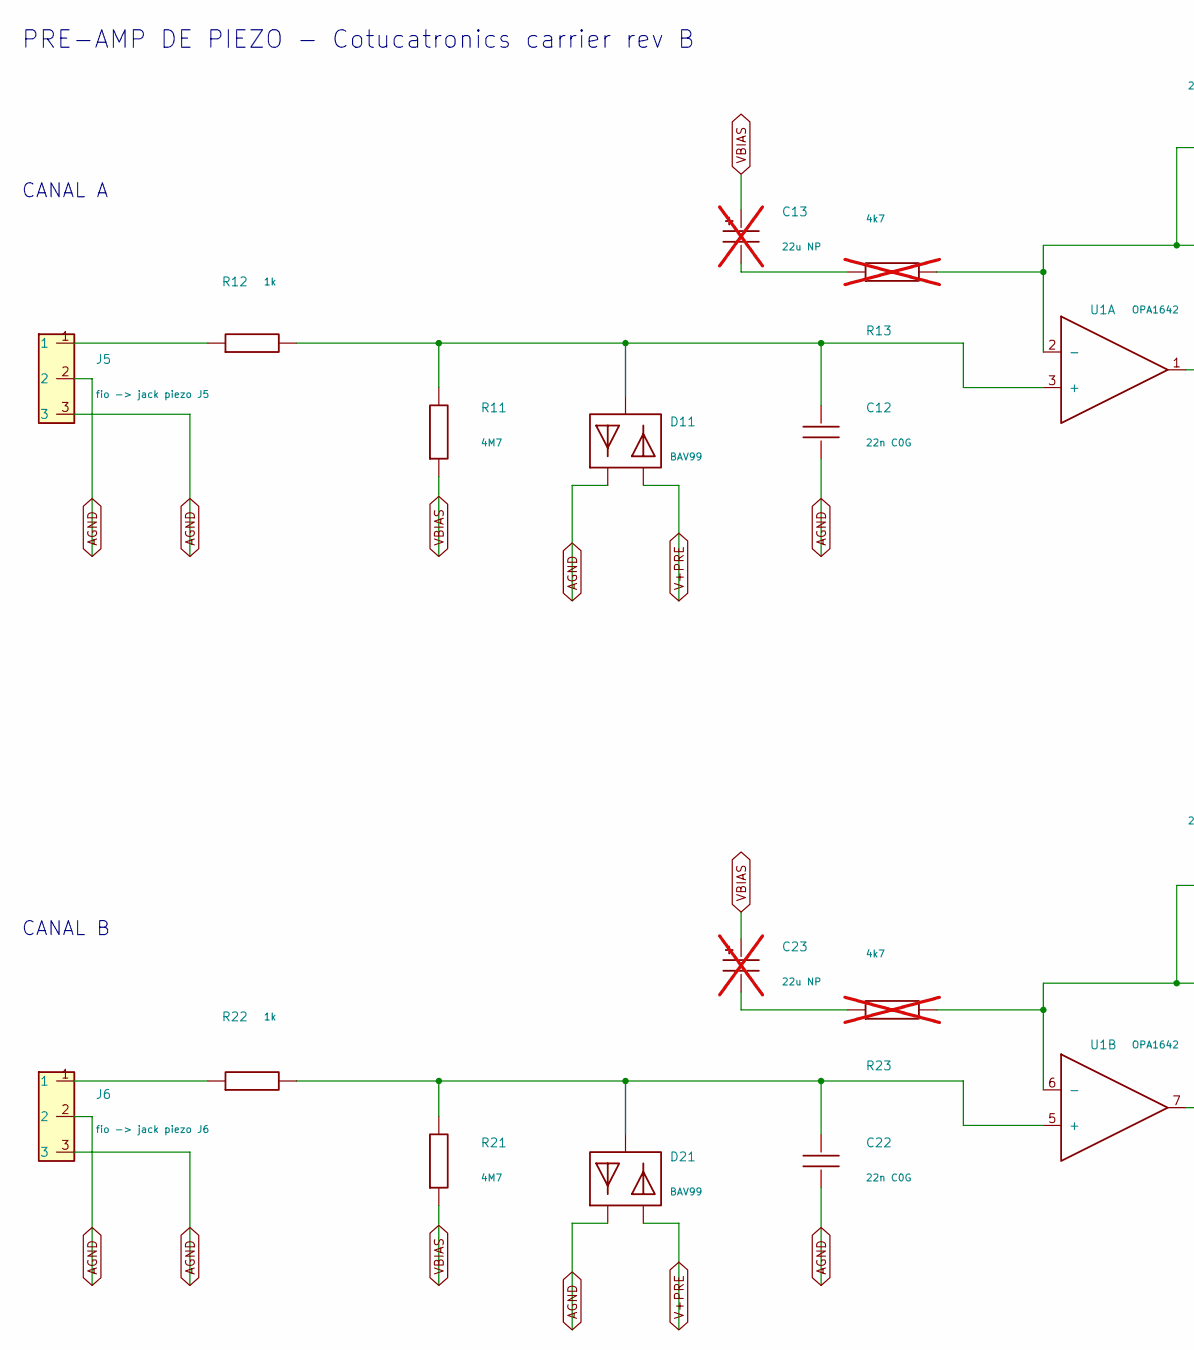
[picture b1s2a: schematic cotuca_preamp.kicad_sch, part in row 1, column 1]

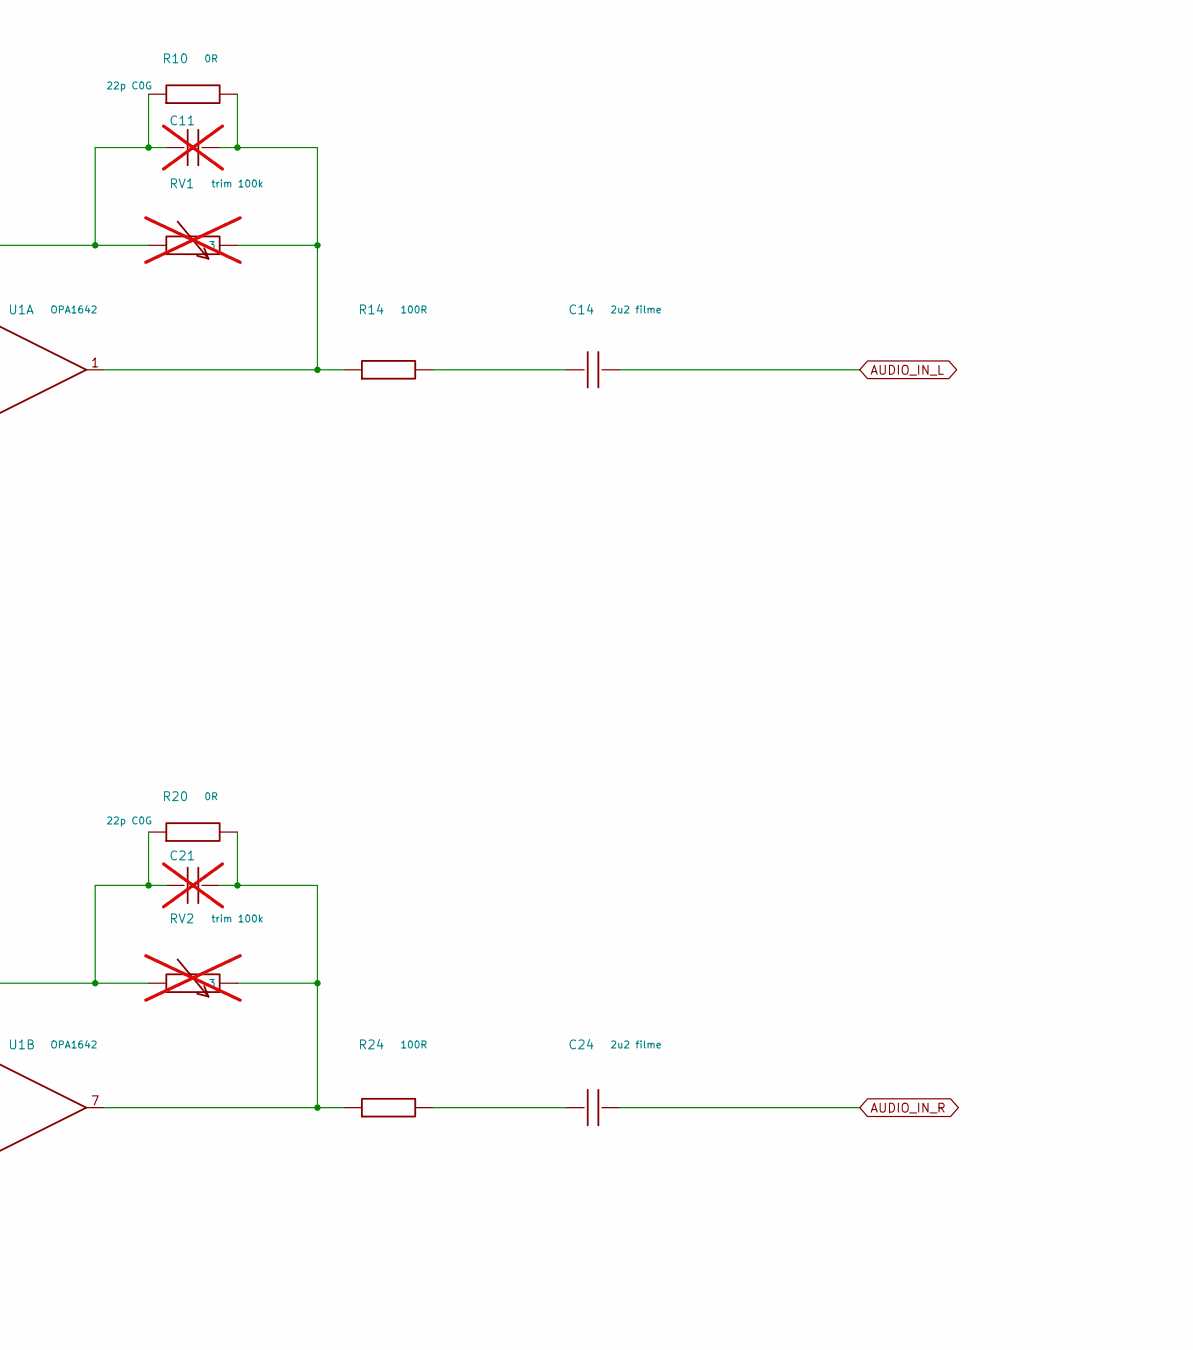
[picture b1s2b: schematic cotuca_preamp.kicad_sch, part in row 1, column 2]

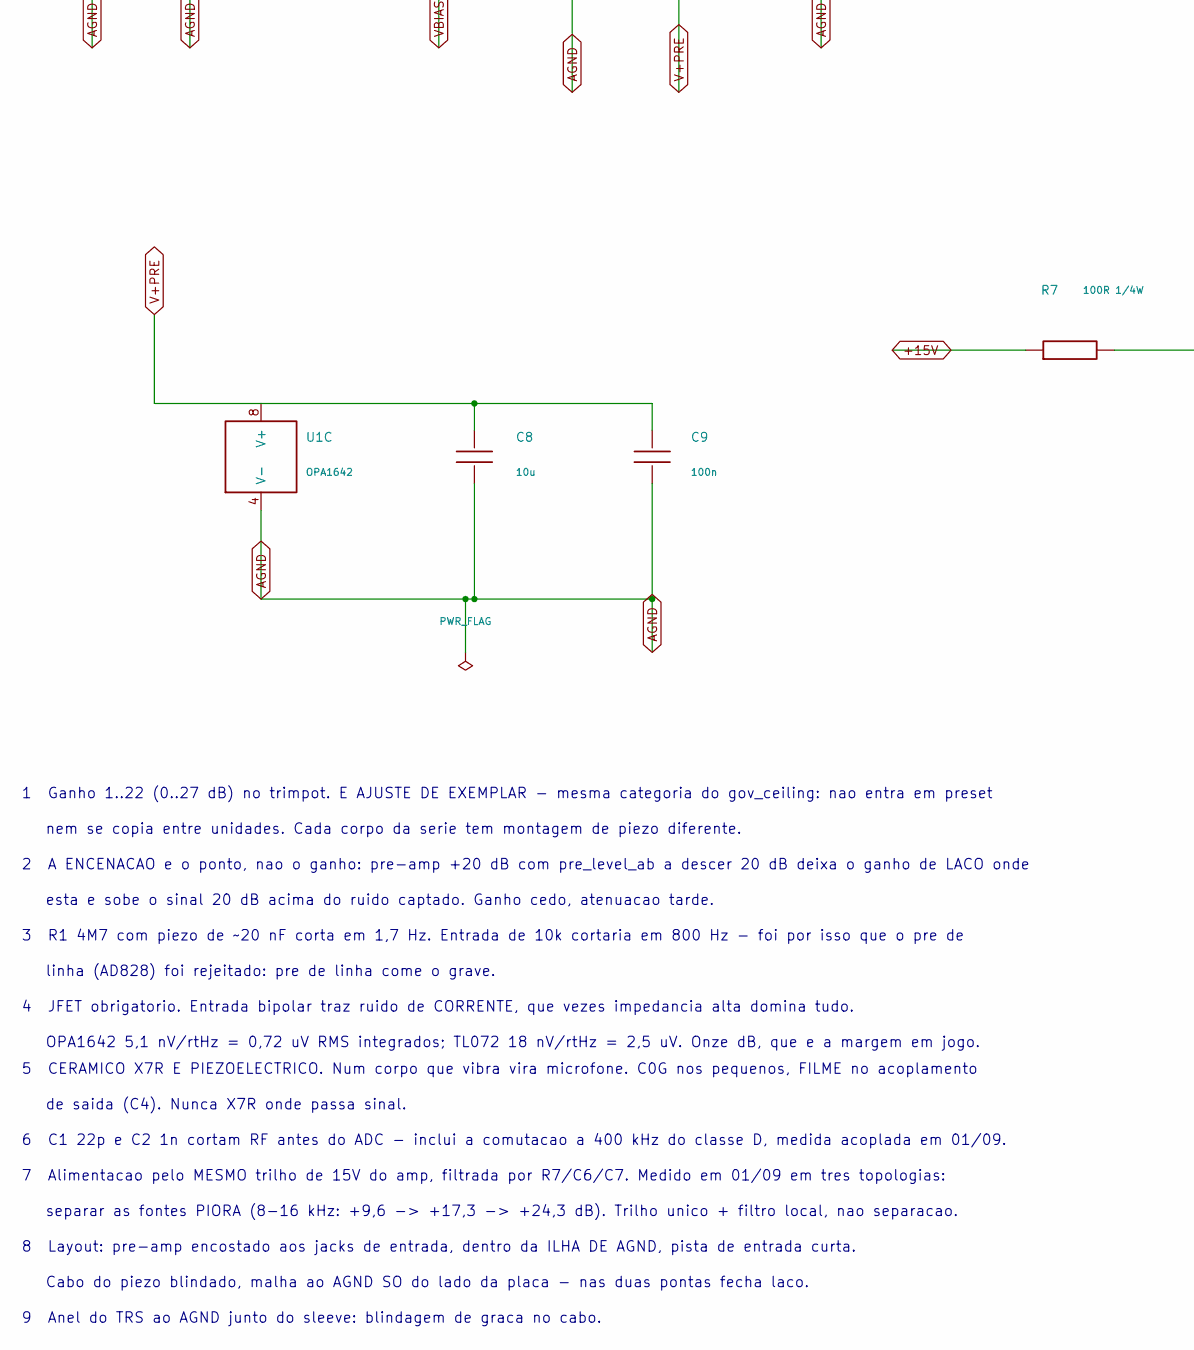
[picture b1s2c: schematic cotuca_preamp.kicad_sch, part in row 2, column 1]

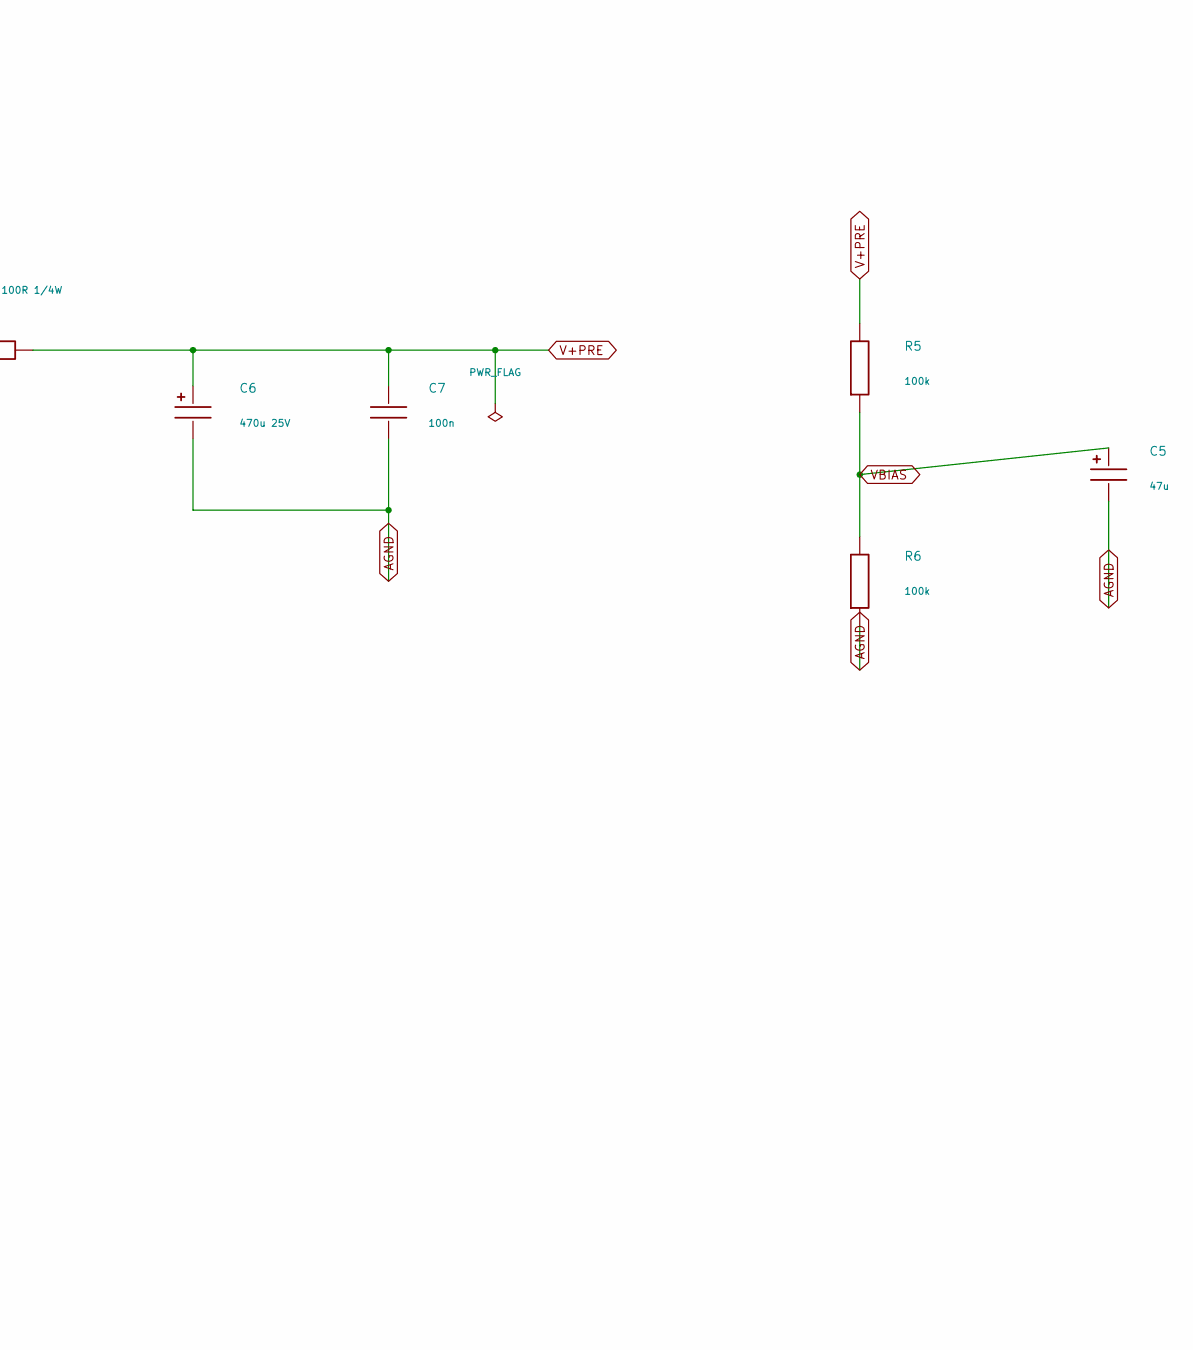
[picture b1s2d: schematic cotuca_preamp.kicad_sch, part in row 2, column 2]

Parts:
C5: 47u; CP_Radial_D6.3mm_P2.50mm; MPN EEU-FR1E470
C6: 470u 25V; CP_Radial_D10.0mm_P5.00mm; MPN EEU-FR1E471
C7, C9: 100n; C_0805_2012Metric
C8: 10u; C_1206_3216Metric; MPN CL31B106KAHNNWE
C11, C21: 22p C0G; C_0805_2012Metric; not fitted
C12, C22: 22n C0G; C_1206_3216Metric; MPN C1206C223J5GACTU
C13, C23: 22u NP; CP_Radial_D6.3mm_P2.50mm; MPN UES1H220MEM; not fitted
C14, C24: 2u2 filme; C_Rect_L7.2mm_W11.0mm_P5.00mm_FKS2_FKP2_MKS2_MKP2; MPN MKS2C042201M00KN00
D11, D21: BAV99; SOT-23; MPN BAV99,215
J5: fio -> jack piezo J5; PinHeader_1x03_P2.54mm_Vertical; MPN 61304011121
J6: fio -> jack piezo J6; PinHeader_1x03_P2.54mm_Vertical; MPN 61304011121
R5, R6: 100k; R_0805_2012Metric
R7: 100R 1/4W; R_1206_3216Metric
R10, R20: 0R; R_0805_2012Metric
R11, R21: 4M7; R_0805_2012Metric
R12, R22: 1k; R_0805_2012Metric
R13, R23: 4k7; R_0805_2012Metric; not fitted
R14, R24: 100R; R_0805_2012Metric
RV1, RV2: trim 100k; Potentiometer_Bourns_3296W_Vertical; MPN 3296W-1-104LF; not fitted
U1: OPA1642; SOIC-8_3.9x4.9mm_P1.27mm; MPN OPA1642AIDR

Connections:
+15V: R7.1; also elsewhere on the board
AGND: C5.2, C6.2, C7.2, C8.2, C9.2, C12.2, C22.2, D11.1, D21.1, J5.2, J5.3, J6.2, J6.3, R6.2, U1.4 (V-); also elsewhere on the board
AUDIO_IN_L: C14.2; also elsewhere on the board
AUDIO_IN_R: C24.2; also elsewhere on the board
unnamed: C11.2, R10.2, R14.1, RV1.2, RV1.3, U1.1
unnamed: C13.2, R13.1
unnamed: C14.1, R14.2
unnamed: C21.2, R20.2, R24.1, RV2.2, RV2.3, U1.7
unnamed: C23.2, R23.1
unnamed: C24.1, R24.2
unnamed: J5.1, R12.1
unnamed: J6.1, R22.1
unnamed: C12.1, D11.3, R11.1, R12.2, U1.3 (+)
unnamed: C11.1, R10.1, R13.2, RV1.1, U1.2 (-)
unnamed: C22.1, D21.3, R21.1, R22.2, U1.5 (+)
unnamed: C21.1, R20.1, R23.2, RV2.1, U1.6 (-)
V+PRE: C6.1, C7.1, C8.1, C9.1, D11.2, D21.2, R5.1, R7.2, U1.8 (V+); also elsewhere on the board
VBIAS: C5.1, C13.1, C23.1, R5.2, R6.1, R11.2, R21.2; also elsewhere on the board

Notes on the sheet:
9 Anel do TRS ao AGND junto do sleeve: blindagem de graca no cabo.
separar as fontes PIORA (8-16 kHz: +9,6 -> +17,3 -> +24,3 dB). Trilho unico + filtro local, nao separacao.
esta e sobe o sinal 20 dB acima do ruido captado. Ganho cedo, atenuacao tarde.
2 A ENCENACAO e o ponto, nao o ganho: pre-amp +20 dB com pre_level_ab a descer 20 dB deixa o ganho de LACO onde
6 C1 22p e C2 1n cortam RF antes do ADC - inclui a comutacao a 400 kHz do classe D, medida acoplada em 01/09.
CANAL B
3 R1 4M7 com piezo de ~20 nF corta em 1,7 Hz. Entrada de 10k cortaria em 800 Hz - foi por isso que o pre de
nem se copia entre unidades. Cada corpo da serie tem montagem de piezo diferente.
de saida (C4). Nunca X7R onde passa sinal.
8 Layout: pre-amp encostado aos jacks de entrada, dentro da ILHA DE AGND, pista de entrada curta.
7 Alimentacao pelo MESMO trilho de 15V do amp, filtrada por R7/C6/C7. Medido em 01/09 em tres topologias:
PRE-AMP DE PIEZO - Cotucatronics carrier rev B
Cabo do piezo blindado, malha ao AGND SO do lado da placa - nas duas pontas fecha laco.
linha (AD828) foi rejeitado: pre de linha come o grave.
OPA1642 5,1 nV/rtHz = 0,72 uV RMS integrados; TL072 18 nV/rtHz = 2,5 uV. Onze dB, que e a margem em jogo.
CANAL A
4 JFET obrigatorio. Entrada bipolar traz ruido de CORRENTE, que vezes impedancia alta domina tudo.
1 Ganho 1..22 (0..27 dB) no trimpot. E AJUSTE DE EXEMPLAR - mesma categoria do gov_ceiling: nao entra em preset
5 CERAMICO X7R E PIEZOELECTRICO. Num corpo que vibra vira microfone. C0G nos pequenos, FILME no acoplamento
